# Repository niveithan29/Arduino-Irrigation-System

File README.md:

# Arduino-Irrigation-System
Arduino based Plant-Watering System w/ Bluetooth Connectivity

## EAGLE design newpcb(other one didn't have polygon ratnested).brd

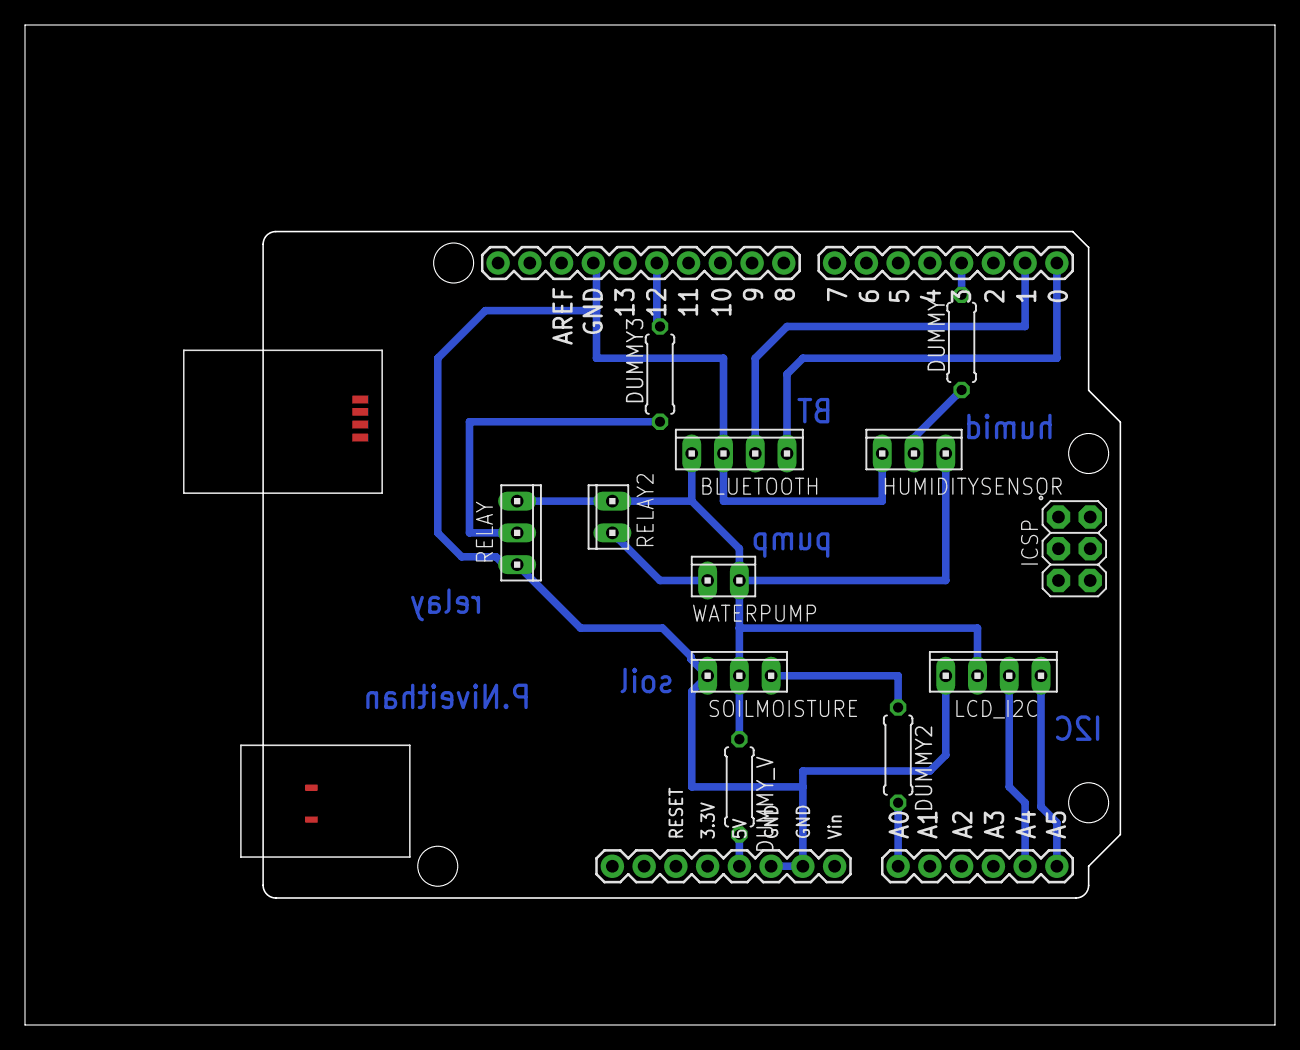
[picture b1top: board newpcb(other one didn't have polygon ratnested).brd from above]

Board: 2 copper layers, 100.0 x 80.0 mm, 12 parts (0 on the bottom side), 14 nets.

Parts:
BLUETOOTH: 10X04MTA
DUMMY, DUMMY2, DUMMY3: 0; 0207/7
DUMMY_V: 0; 0207/7
HUMIDITYSENSOR: 10X03MTA
LCD_I2C: 10X04MTA
PCB1: ARDUINO_UNO
RELAY: 10X03MTA
RELAY2: 10X02MTA
SOILMOISTURE: 10X03MTA
WATERPUMP: 10X02MTA

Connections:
5V: BLUETOOTH.4, DUMMY_V.1, HUMIDITYSENSOR.1, LCD_I2C.3, RELAY.3, RELAY2.1, SOILMOISTURE.2, WATERPUMP.1
GND: BLUETOOTH.3, HUMIDITYSENSOR.3, LCD_I2C.4, PCB1.GND, PCB1.GND., PCB1.GND.., RELAY.1, SOILMOISTURE.3
unnamed: DUMMY_V.2, PCB1.5V
unnamed: DUMMY2.1, SOILMOISTURE.1
unnamed: DUMMY.1, HUMIDITYSENSOR.2
unnamed: DUMMY3.1, RELAY.2
PIN0: BLUETOOTH.1, PCB1.0
PIN1: BLUETOOTH.2, PCB1.1
PIN3: DUMMY.2, PCB1.3
PIN12: DUMMY3.2, PCB1.12
PUMP: RELAY2.2, WATERPUMP.2
SCL: LCD_I2C.1, PCB1.A5
SDA: LCD_I2C.2, PCB1.A4
SOIL: DUMMY2.2, PCB1.A0

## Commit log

2021-10-25 Rename newpcb(other one didn't have polygon ratnested).brd to PCB SHIELD
